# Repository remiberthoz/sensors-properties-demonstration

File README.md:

# Simulated absorbance sensors

This program simulates a series of light intensity sensors based on a single
physical sensor. It is designed primarily for educational purposes to teach
biology or chemistry students about sensor properties. Simulated sensors have
different properties (linearity, sensitivity, range, response time, noise).
The program visualizes the behavior of these simulated sensors in real-time,
allowing for a hands-on, inexpensive way to discover these concepts.

## Problems to fix / todo list...

- The calibration procedure is not OK, it should somehow take the value of
  MAX_A into account ; and likely the complete scaling (with to_byte).

- Lower the Baud rate to make the transmission more robust with poor-quality
  USB cables.

- Try to output sensor values on DAC such that the students can work on an
  oscilloscope. Check if the DAC communication rate is good enough to
  simulate real analog.

- Program Arduino IO to read jumper status, and potentially allow students to
  change easily configuration.

## TECHNICAL REQUIREMENTS

### Hardware

The program is designed to run on an Arduino Uno board (or compatible) fitted
whith a companion shield that holds a light source, a light sensor, and a
sample holder for spectrophotometry cuvettes.

The light source and the sensor are positioned approximately 1 cm apart,
separated by the cuvette holder, which is used to adjust light intensities on
the sensor.

Refer to the schematic for connections and for part numbers that I used (also
see below). The cuvette holder was 3d printed, the 3d model is available.

#### Details on parts and wavelength choices

I decided to work with infrared light (935 +/- 25) nm to limit interference
from modern indoor lighting sources. I used a IR LED, OP140D with a 470R
resitor ; and a wavelength-matched OP550A IR NPN phototransitor kept in
linear regime using a 1k resistor on the emitter side.

Samples absorbing in infrared can easily be prepared with aqueous solutions
of copper sulfate. To avoid spills in the electronic lab, I mixed solutions
of copper sulfate with a preparation of 1 % agarose. It gelifies and stays in
the cuvettes.

Hydrated copper sulfate and agarose gel both absorb at 935 nm. The absorbance
of these prepared samples can be measured with a reference spectrophotometer.

### Software

This Arduino program works in tandem with a companion python program, which
runs on a computer to:

- Read data from the Arduino, through serial communication.
- Display a live graph of the sensors readings.

## Objective

This setup aims to teach students about sensor properties such as:

- Linearity
- Sensitivity
- Range (low and high saturations)
- Response time
- Noise

Students will visualize the response of several simulated sensors in
real-time. These sensors outputs are derived from the output of the physical
sensor, giving a sense of reality to the simulation (simulated sensors will
respond to change of absorbance standards, ambient light, light path
obstruction, ...).

This exercise allows students to explore how different sensors react to the
same physical change, producing different electrical outputs. Students can
create output-input graphs, measure response time, and compare sensors.

Instructors can adjust the sensors properties by change in code, rather than
by buying and mounting various sensors.

## Simulated sensors are *absorbance sensors*

In the context of biology and chemistry courses, students are typically
introduced to the concept of absorbance, often via spectrophotometry. Since
this concept is well known, and thus more intuitive than light intensity,
the sensors outputs a quantity linked to absorbance rather than light 
intensities (even though it really measures light intensities). This makes
it similar to how spectrophotometers usually work.

## Calibration

The setup can be calibrated by the instructors using samples of known
absorbance. Adjustements in the code can be made such that the Arduino
program can determine true absorbance internally, before deriving the output
values of simulated sensors.

Indeed, the sensor used on the Arduino shield is not necessarely linear
against light intensity itself.

## Prerequisites for students

Before using this system, students should:

- Understand the concept of absorbance as a property of a sample.
- Know that electronic sensors measure an electrical quantity (e.g., voltage,
  current), which is then mapped to physical parameters like absorbance.

These two facts explain why the output values are all different for a single
sample.

Students do not need to know that there is only one physical sensor in the
system. The setup can be presented as if multiple sensors are being used,
each with different response characteristics.

## Students focus on sensor characteristics

The main teaching goal is for students to understand how different sensors
behave, not how absorbance relates to light intensity. The system abstracts
this relationship by presenting data as voltage outputs (mapped to real
absorbance values via calibration). Students can focus on sensor
characteristics. This knowledge can later be transferred to any type of
sensor.

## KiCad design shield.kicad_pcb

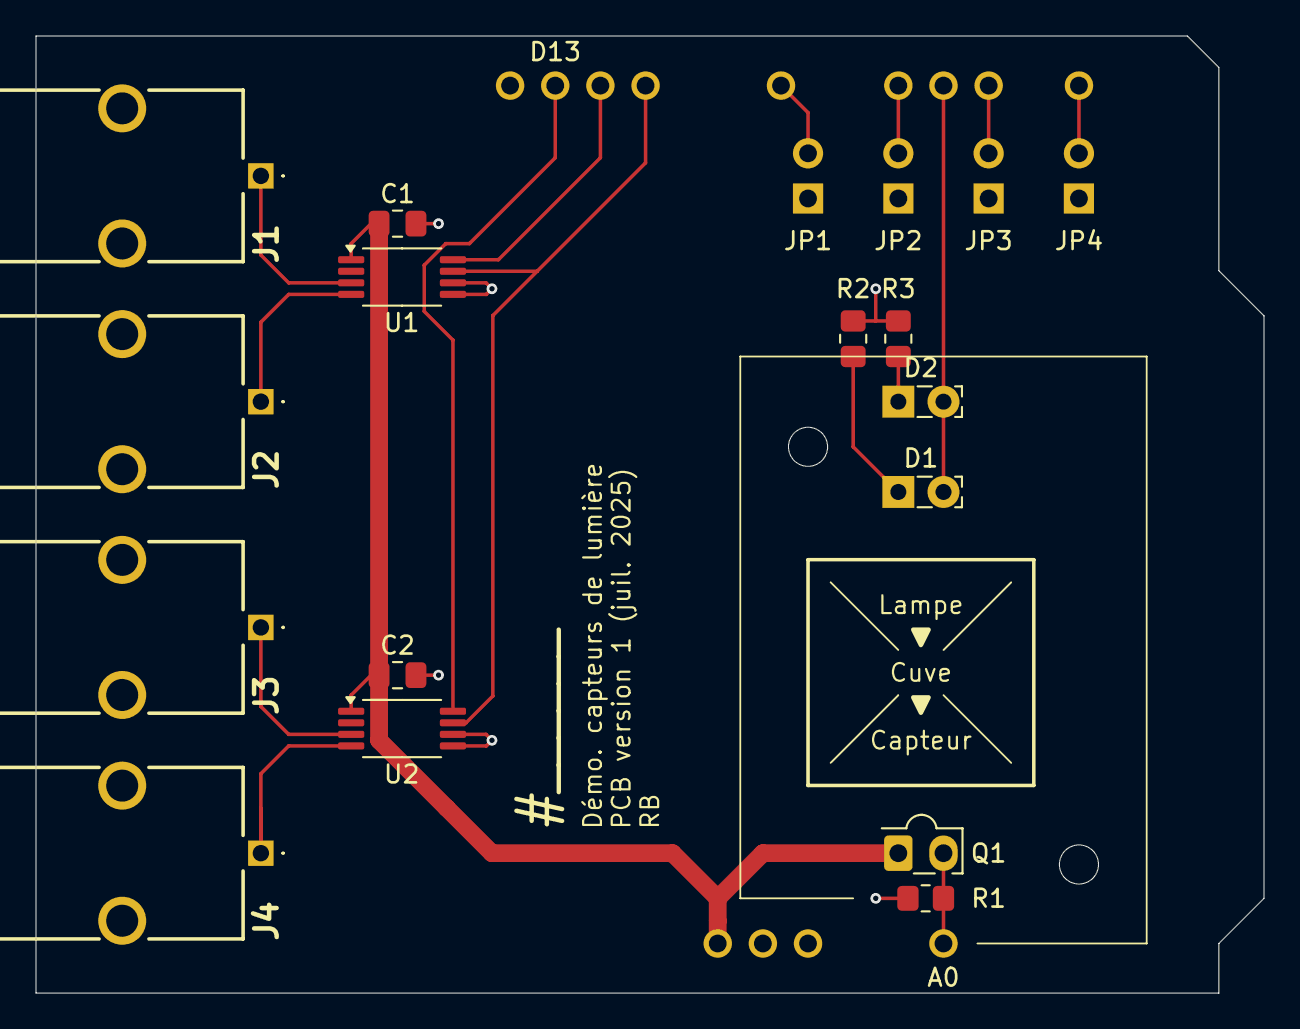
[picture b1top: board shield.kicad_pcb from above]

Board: 2 copper layers, 69.1 x 53.8 mm, 19 parts (1 on the bottom side), 17 nets.

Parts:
A1: Arduino_UNO_R3
C1, C2: C; C_0805_2012Metric_Pad1.18x1.45mm_HandSolder
D1: OP140D (IR); LED_SideEmitter_Rectangular_W4.5mm_H1.6mm
D2: LTL-307P (Red); LED_SideEmitter_Rectangular_W4.5mm_H1.6mm
J1, J2, J3, J4: Conn_Coaxial; 731713150
JP1, JP2, JP3, JP4: Jumper_2_Open; PinHeader_1x02_P2.54mm_Vertical
Q1: OP550A (IR); Osram_LPT80A
R1: 10k; R_0805_2012Metric_Pad1.20x1.40mm_HandSolder
R2, R3: 220 min; R_0805_2012Metric_Pad1.20x1.40mm_HandSolder
U1, U2: TSSOP-8_4.4x3mm_P0.65mm

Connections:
/ANALOG1: J1.1 (In), U1.3 (VOUT0)
/ANALOG2: J2.1 (In), U1.4 (VOUT1)
/ANALOG3: J3.1 (In), U2.3 (VOUT0)
/ANALOG4: J4.1 (In), U2.4 (VOUT1)
/ANALOG_SENSE: A1.9 (A0), Q1.2 (E), R1.1
/LED_CONTROL: A1.20 (D5), D1.2 (A), D2.2 (A)
/SCL: A1.26 (D11), U1.7 (SCL), U2.7 (SCL)
/SDA1: A1.27 (D12), U1.8 (SDA)
/SDA2: A1.28 (D13), U2.8 (SDA)
GND: A1.6 (GND), A1.7 (GND), A1.29 (GND), C1.2, C2.2, J1.2 (Ext), J2.2 (Ext), J3.2 (Ext), J4.2 (Ext), JP1.1 (A), JP2.1 (A), JP3.1 (A), JP4.1 (A), R1.2, R2.2, R3.2, U1.5 (VSS), U1.6 (LAT0/HVC), U2.5 (VSS), U2.6 (LAT0/HVC)
unnamed: A1.17 (D2), JP4.2 (B)
unnamed: A1.19 (D4), JP3.2 (B)
unnamed: A1.21 (D6), JP2.2 (B)
unnamed: A1.23 (D8), JP1.2 (B)
unnamed: D1.1 (K), R2.1
unnamed: D2.1 (K), R3.1
VCC: A1.5 (+5V), C1.1, C2.1, Q1.1 (C), U1.1 (VDD), U2.1 (VDD)

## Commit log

2025-11-09 Add schematic and layout images to README
    Added images of the schematic, layout, and cuvette holder to the README.
2025-11-09 feat: accumulate reads while waiting, then average
    Instead of waiting the next tick doing nothing, we can read sensor
    values and average the results from the whole sampling period.
    This really makes a "sampling period" instead of a "sampling
    interval". It will greately reduce noise on the physical sensor,
    but also lower the response time of the internal "calibrated"
    sensor from that of the physical sensor (few µs) to that of the
2025-11-16 fix: add missing return when not outputing
2025-11-16 docs: check TODO (accumulate slows response time ?)
    Answer, after tests, is that it is not noticeable.
2025-11-16 feat: remove background 'dark' value from measurments
2025-11-16 local: update calibration data for my own boards
2025-11-16 fix: add required argument to button event handler
2025-11-16 chores: remove commented code sections
2025-11-16 doc: add problems to fix / todo list section to README
2025-11-19 doc: indicate new todo list item (Baud rate adjustment)
    Baud rate of 115200 seems too high to work reliably with USB cables in the classroom.
2025-11-25 feat: lower Baud rate, make TX robust for poor USB
    Arduino transmits 1 byte per sensor + 1 byte. With a high estimate
    of 7 sensors (8 bytes to transmit), it takes 6 ms to transmit data
    at a baud rate of 9600 bit/s. This leaves enough time for the
    remainings of the 25 ms period, both on Arduino and on PC, to
    measure and to plot.
2025-11-25 fix: add missing return when not outputing (same as #e988812)
